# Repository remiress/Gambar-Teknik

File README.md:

# Hi I'm Raihan Emir
# I study at the State University of Yogyakarta

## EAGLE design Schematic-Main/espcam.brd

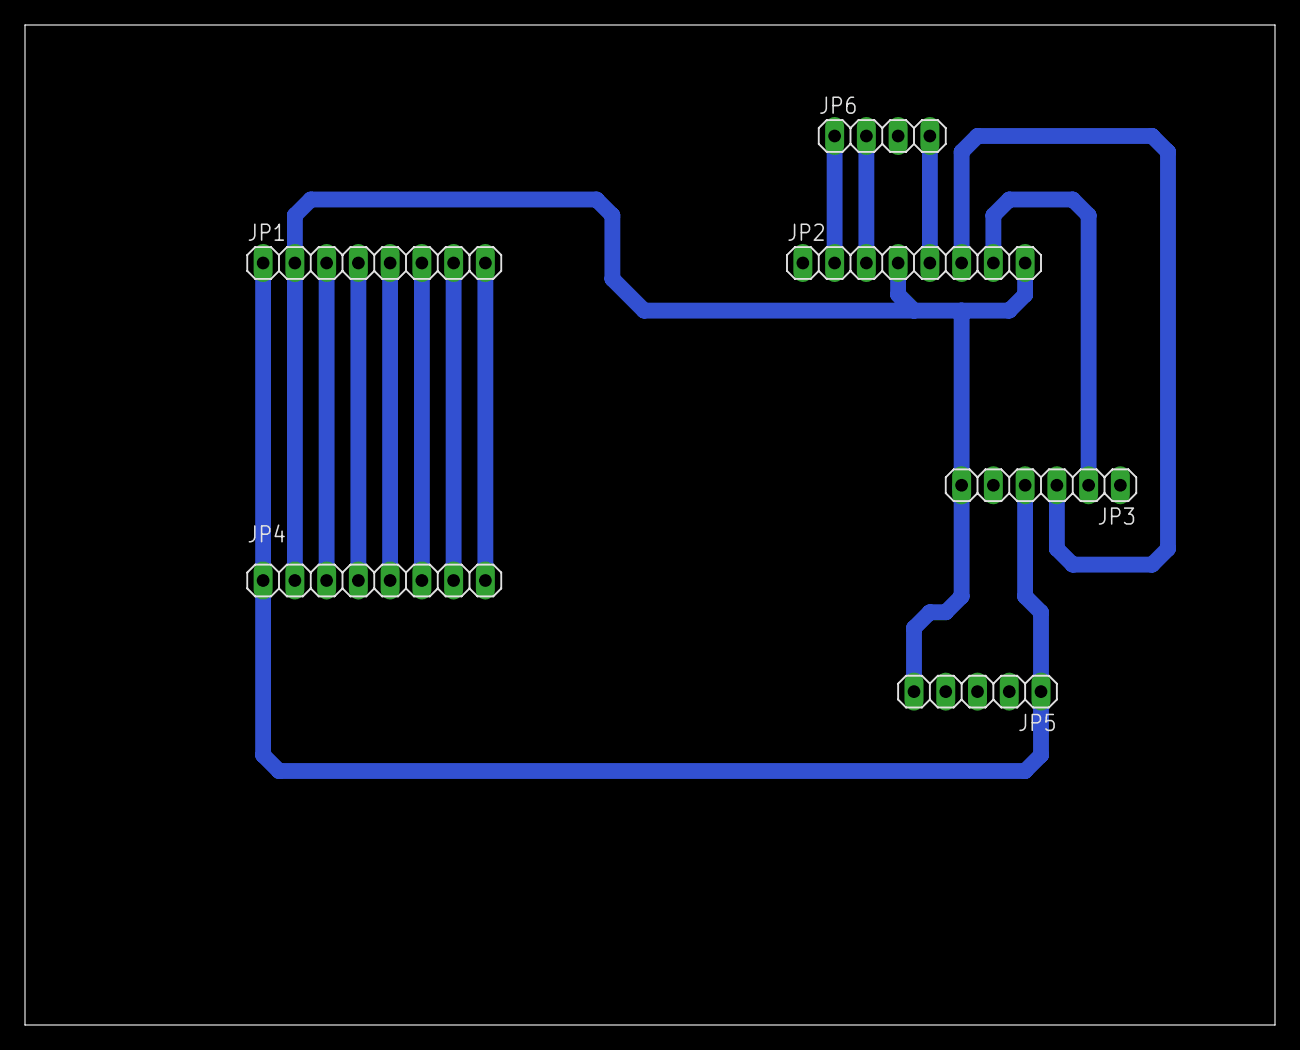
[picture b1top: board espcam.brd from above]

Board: 2 copper layers, 100.0 x 80.0 mm, 6 parts (0 on the bottom side), 13 nets.

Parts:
JP1, JP2, JP4: 1X08
JP3: 1X06
JP5: 1X05
JP6: 1X04

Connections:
5V: JP1.1, JP3.4, JP4.1, JP5.1
GND: JP1.2, JP2.4, JP2.8, JP3.6, JP4.2, JP5.5
IO0: JP2.3, JP6.2
IO2: JP1.7, JP4.7
IO4: JP1.8, JP4.8
IO12: JP1.3, JP4.3
IO13: JP1.4, JP4.4
IO14: JP1.6, JP4.6
IO15: JP1.5, JP4.5
IO16: JP2.2, JP6.1
RX: JP2.7, JP3.2
TX: JP2.6, JP3.3
VOUT: JP2.5, JP6.4

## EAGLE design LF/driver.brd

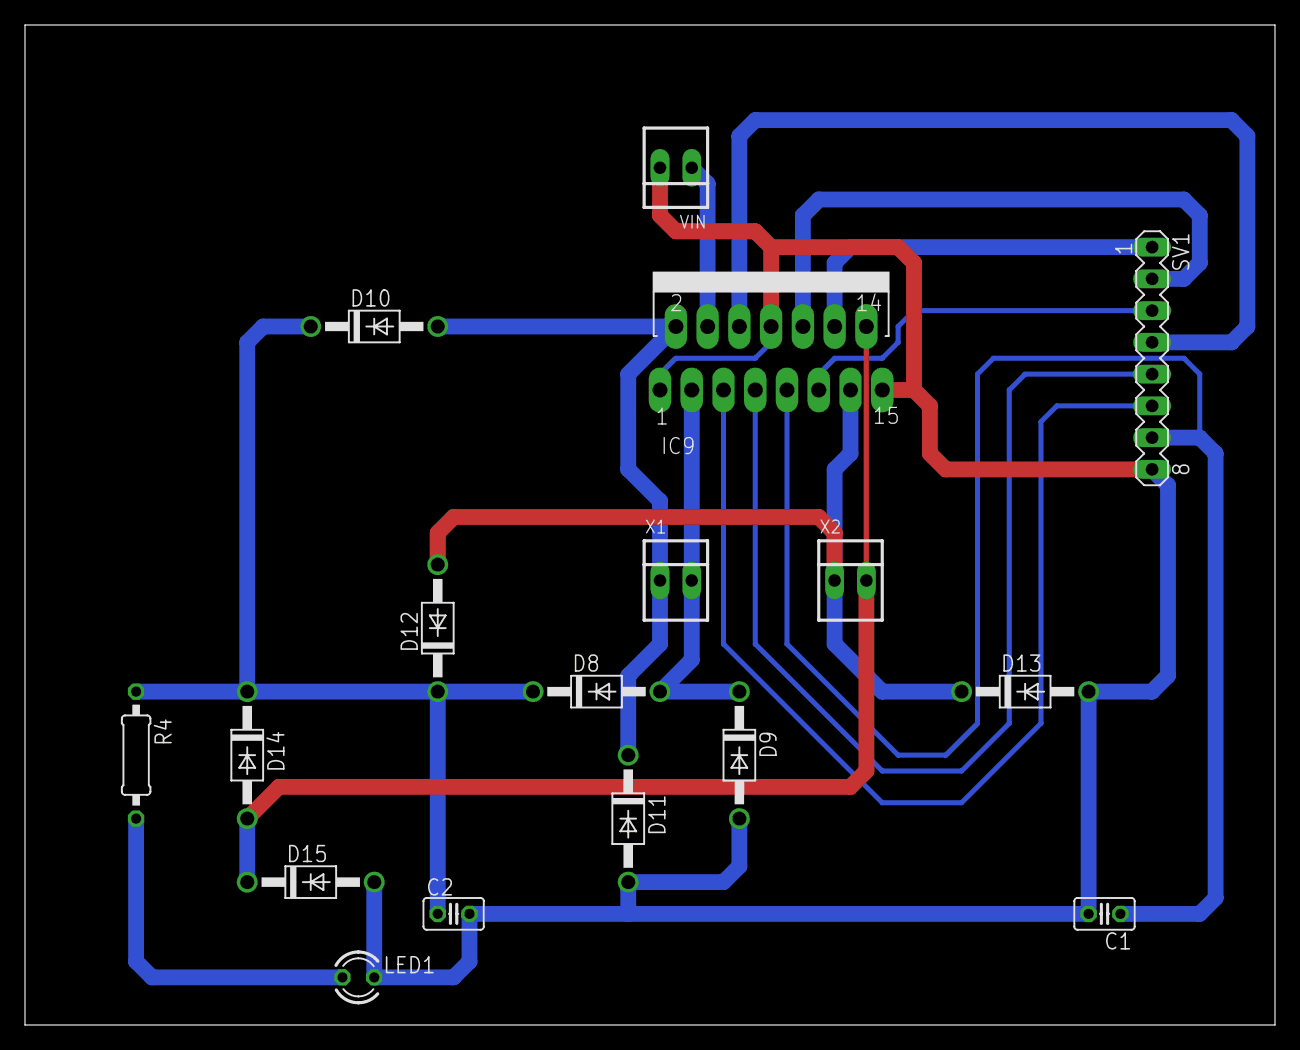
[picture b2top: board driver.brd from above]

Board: 2 copper layers, 100.0 x 80.0 mm, 17 parts (0 on the bottom side), 14 nets.

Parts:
C1, C2: 100nF; C025-025X050
D8, D9, D10, D11, D12, D13, D14, D15: 1N4004; DO41-10
IC9: L298; MULTIWATT-15
LED1: LED3MM
R4: 330; 0207/10
SV1: MA08-1
VIN: 22-23-2021
X1, X2: 22-23-2021

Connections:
GND: C1.2, C2.2, D9.A, D11.A, D13.A, D15.A, IC9.1, IC9.8, IC9.15, LED1.K, SV1.8, VIN.2
unnamed: IC9.5, SV1.6
unnamed: IC9.7, SV1.5
unnamed: IC9.12, SV1.1
unnamed: IC9.10, SV1.2
unnamed: IC9.6, SV1.4
unnamed: IC9.11, SV1.3
unnamed: LED1.A, R4.2
unnamed: D8.A, D9.C, IC9.3, X1.2
unnamed: D10.A, D11.C, IC9.2, X1.1
unnamed: D12.A, D13.C, IC9.13, X2.1
unnamed: D14.A, D15.C, IC9.14, X2.2
VCC: C1.1, IC9.9, SV1.7
VDD: C2.1, D8.C, D10.C, D12.C, D14.C, IC9.4, R4.1, VIN.1

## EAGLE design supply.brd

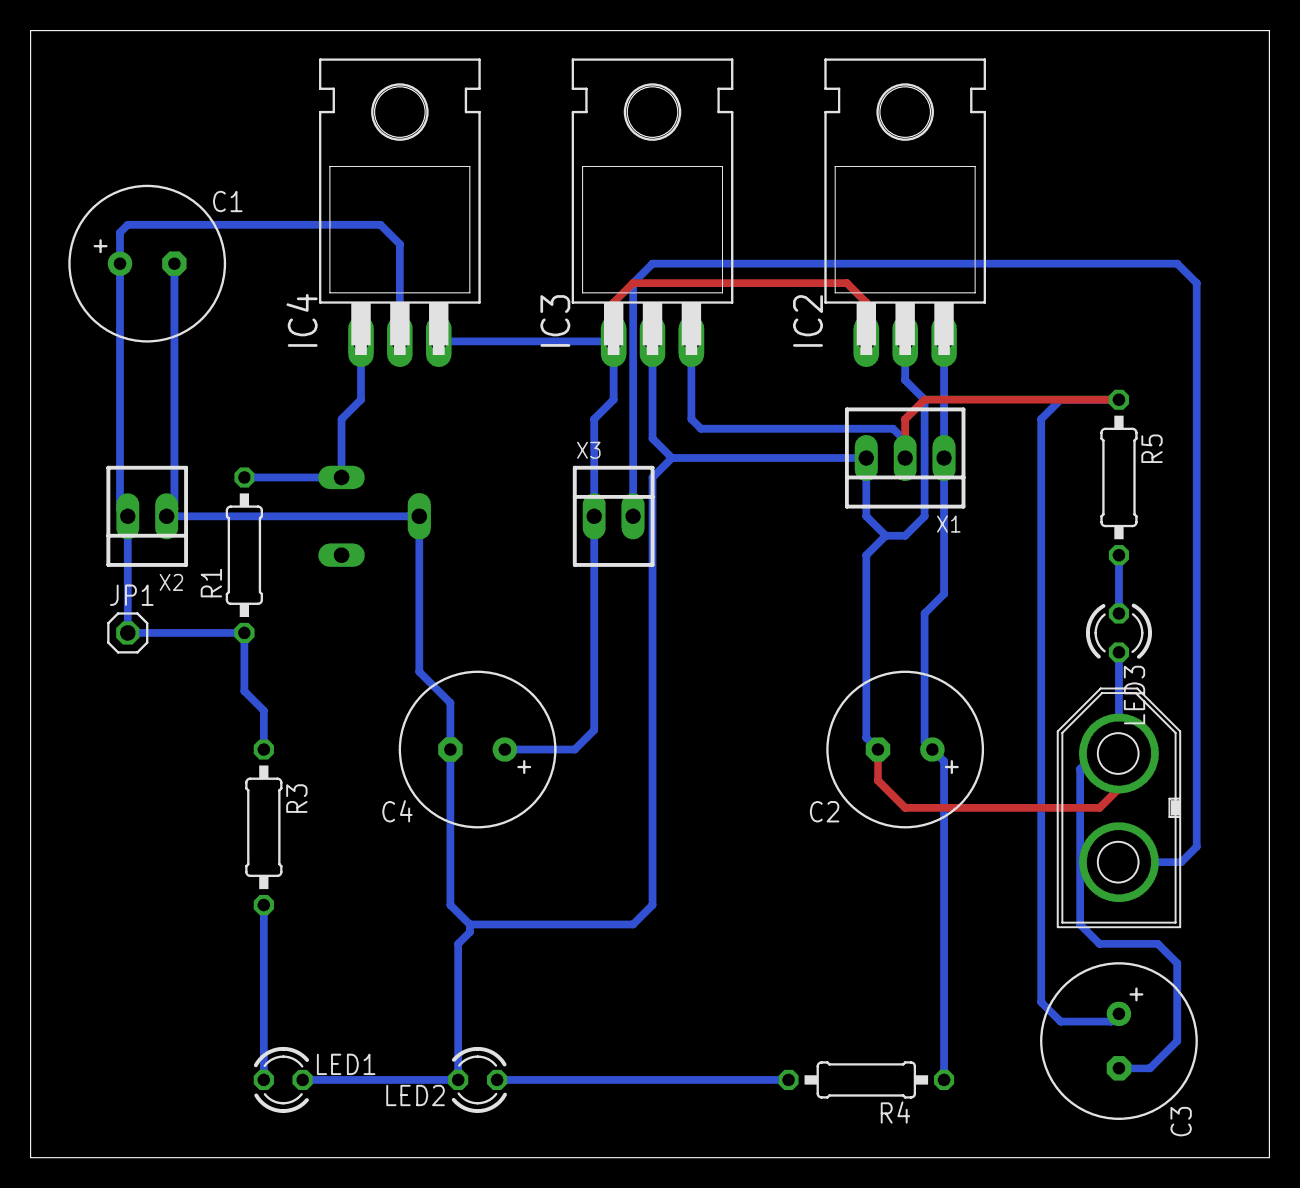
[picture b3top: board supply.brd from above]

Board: 2 copper layers, 81.0 x 73.7 mm, 20 parts (1 on the bottom side), 10 nets.

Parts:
C1, C2, C3, C4: 1000uF/16V; E3,5-10
IC2, IC3: 7805T; TO220H
IC4: 317T; TO220H
JP1: 1X01
LED1, LED2, LED3: LED3MM
R1: 1K2; 0207/10
R2: 20K; CA6V
R3, R4, R5: 1K; 0207/10
VIN: CON-XT60M
X1: VSYS; 22-23-2031
X2: VMOT; 22-23-2021
X3: switch; 22-23-2021

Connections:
+12V: C3.+, IC3.3, R5.1, X1.2
GND: C1.-, C2.-, C3.-, C4.-, IC2.2, IC3.2, LED1.K, LED2.K, LED3.K, R2.S, VIN.V-, X1.3, X2.1
unnamed: IC4.1, R1.2, R2.E
unnamed: LED1.A, R3.2
unnamed: LED3.A, R5.2
unnamed: VIN.V+, X3.2
unnamed: LED2.A, R4.2
VCC: C2.+, IC2.3, R4.1, X1.1
VDD: C1.+, IC4.2, JP1.1, R1.1, R3.1, X2.2
VPP: C4.+, IC2.1, IC3.1, IC4.3, X3.1

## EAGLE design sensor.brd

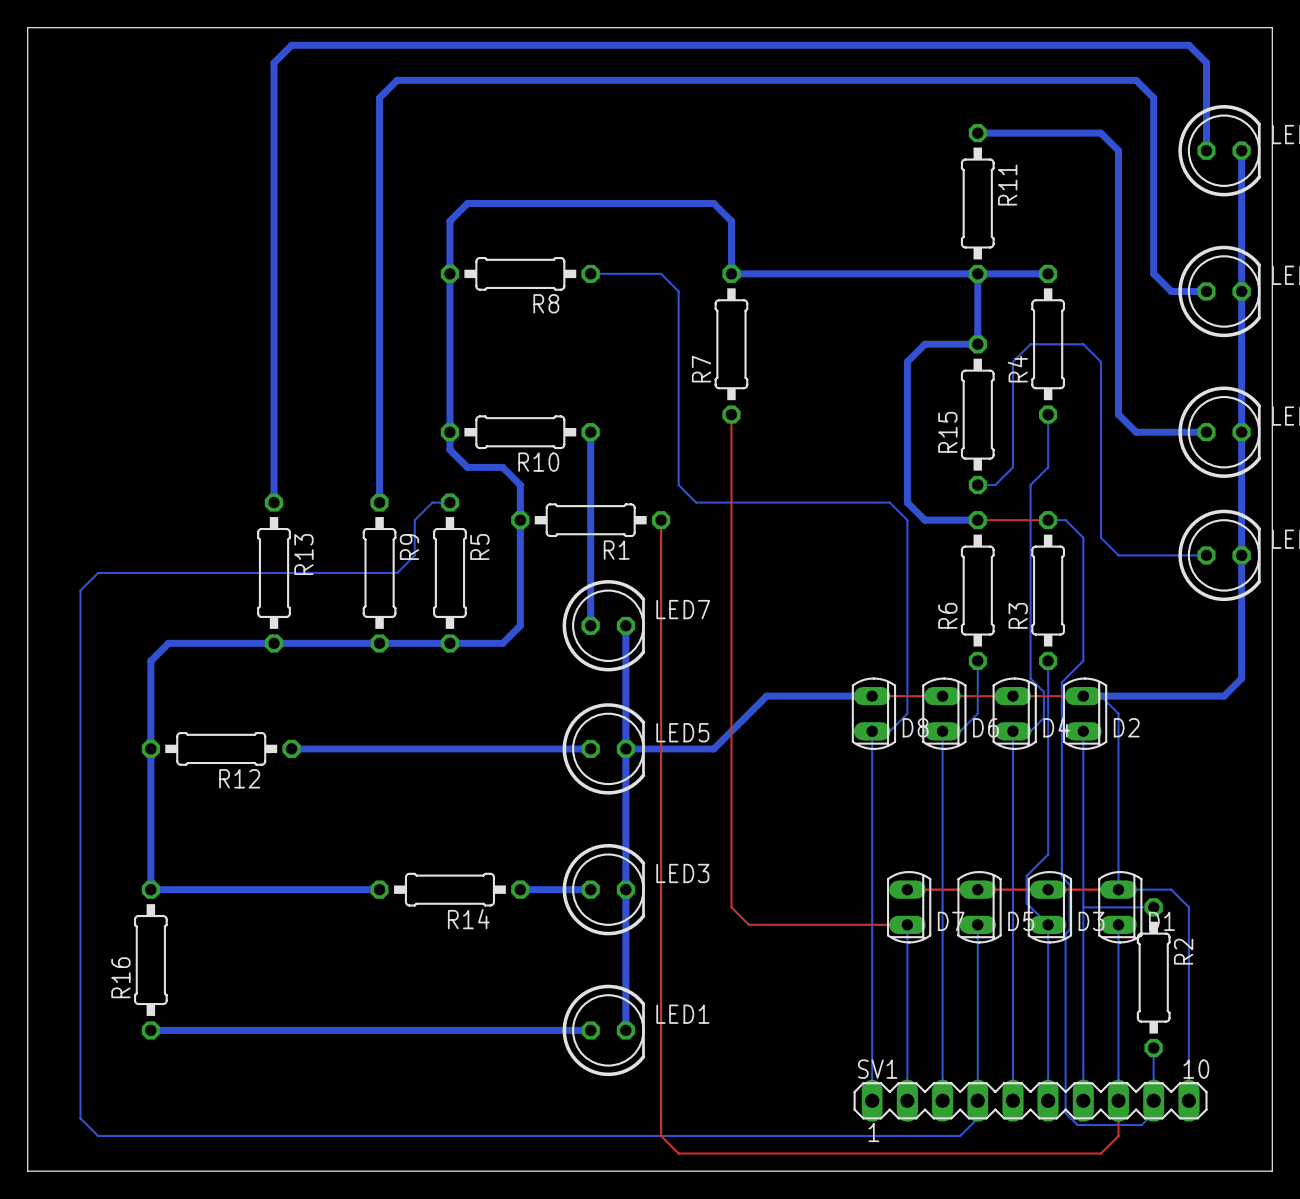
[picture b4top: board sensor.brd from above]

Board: 2 copper layers, 89.8 x 82.5 mm, 33 parts (0 on the bottom side), 18 nets.

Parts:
D1, D2, D3, D4, D5, D6, D7, D8: PhotoDioda; SFH225
LED1, LED2, LED3, LED4, LED5, LED6, LED7, LED8: LED putih SB; LED5MM
R1, R2, R3, R4, R5, R6, R7, R8: 0207/10
R9, R10, R11, R12, R13, R14, R15, R16: 330; 0207/10
SV1: MA10-1

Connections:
GND: D1.A, D2.A, D3.A, D4.A, D5.A, D6.A, D7.A, D8.A, LED1.K, LED2.K, LED3.K, LED4.K, LED5.K, LED6.K, LED7.K, LED8.K, SV1.10
unnamed: LED7.A, R10.1
unnamed: D7.K, R7.1, SV1.2
unnamed: D8.K, R8.1, SV1.1
unnamed: D1.K, R1.1, SV1.8
unnamed: D2.K, R2.1, SV1.7
unnamed: D3.K, R3.1, SV1.6
unnamed: D5.K, R5.1, SV1.4
unnamed: D4.K, R4.1, SV1.5
unnamed: D6.K, R6.1, SV1.3
unnamed: LED6.A, R11.1
unnamed: LED5.A, R12.1
unnamed: LED4.A, R13.1
unnamed: LED3.A, R14.1
unnamed: LED2.A, R15.1
unnamed: LED1.A, R16.1
unnamed: LED8.A, R9.1
VCC: R1.2, R2.2, R3.2, R4.2, R5.2, R6.2, R7.2, R8.2, R9.2, R10.2, R11.2, R12.2, R13.2, R14.2, R15.2, R16.2, SV1.9

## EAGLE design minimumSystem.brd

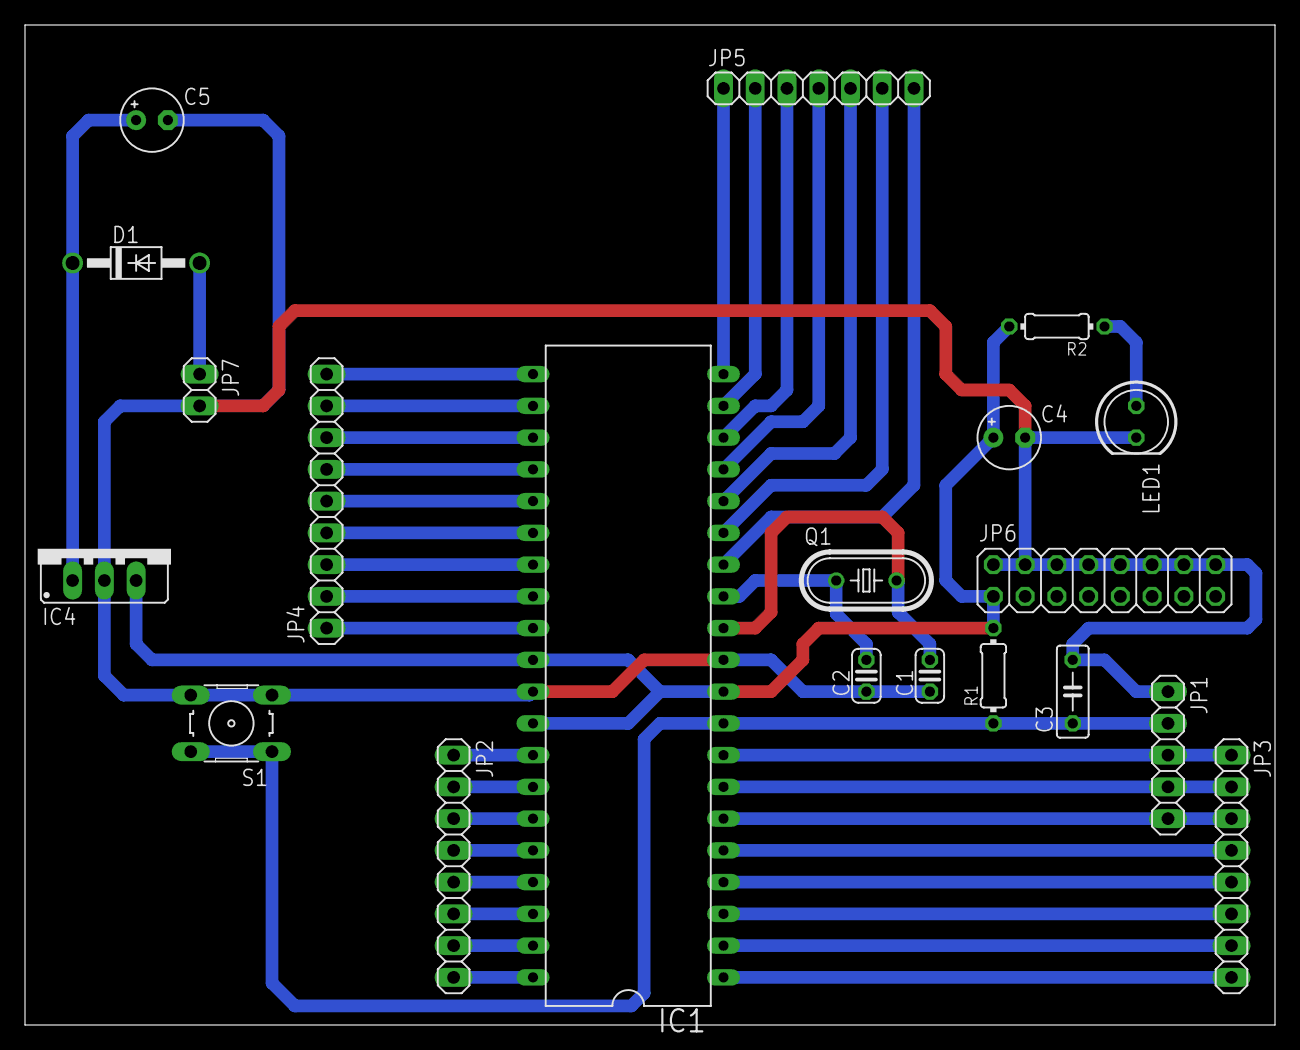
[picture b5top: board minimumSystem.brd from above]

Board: 2 copper layers, 100.0 x 80.0 mm, 20 parts (0 on the bottom side), 40 nets.

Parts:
C1, C2: C025-024X044
C3: C050-025X075
C4, C5: E2,5-5
D1: 1N4004; DO41-10
IC1: MEGA16-P; DIL40
IC4: 78XXS
JP1: 1X05
JP2, JP3: 1X08
JP4: 1X09
JP5: 1X07
JP6: 2X08
JP7: 1X02
LED1: LED5MM
Q1: HC49U-V
R1, R2: 0204/7
S1: B3F-10XX

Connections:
+5V: C4.+, IC1.10, IC1.30, IC1.32, IC4.OUT, JP6.1, JP6.3, JP6.5, JP6.7, JP6.9, JP6.11, JP6.13, JP6.15, R1.2, R2.2
+12V: D1.A, JP7.1
C0: IC1.22, JP4.8
C1: IC1.23, JP4.7
C2: IC1.24, JP4.6
C3: IC1.25, JP4.5
D7: IC1.14, JP5.7
GND: C1.1, C2.1, C3.2, C4.-, C5.-, IC1.11, IC1.31, IC4.GND, JP1.1, JP6.2, JP6.4, JP6.6, JP6.8, JP6.10, JP6.12, JP6.14, JP6.16, JP7.2, LED1.K, S1.3, S1.4
unnamed: IC1.33, JP2.1
unnamed: IC1.34, JP2.2
unnamed: IC1.35, JP2.3
unnamed: IC1.36, JP2.4
unnamed: IC1.37, JP2.5
unnamed: IC1.38, JP2.6
unnamed: IC1.39, JP2.7
unnamed: IC1.40, JP2.8
unnamed: IC1.29, JP4.1
unnamed: IC1.28, JP4.2
unnamed: IC1.27, JP4.3
unnamed: IC1.5, JP3.4
unnamed: IC1.20, JP5.1
unnamed: IC1.19, JP5.2
unnamed: IC1.26, JP4.4
unnamed: IC1.6, JP1.5, JP3.3
unnamed: IC1.4, JP3.5
unnamed: IC1.3, JP3.6
unnamed: IC1.2, JP3.7
unnamed: IC1.1, JP3.8
unnamed: C5.+, D1.C, IC4.IN
unnamed: IC1.15, JP5.6
unnamed: IC1.16, JP5.5
unnamed: IC1.17, JP5.4
unnamed: C3.1, IC1.9, JP1.2, R1.1, S1.1, S1.2
unnamed: IC1.18, JP5.3
unnamed: C1.2, IC1.12, Q1.2
unnamed: C2.2, IC1.13, Q1.1
unnamed: LED1.A, R2.1
unnamed: IC1.8, JP1.3, JP3.1
unnamed: IC1.7, JP1.4, JP3.2
RS: IC1.21, JP4.9

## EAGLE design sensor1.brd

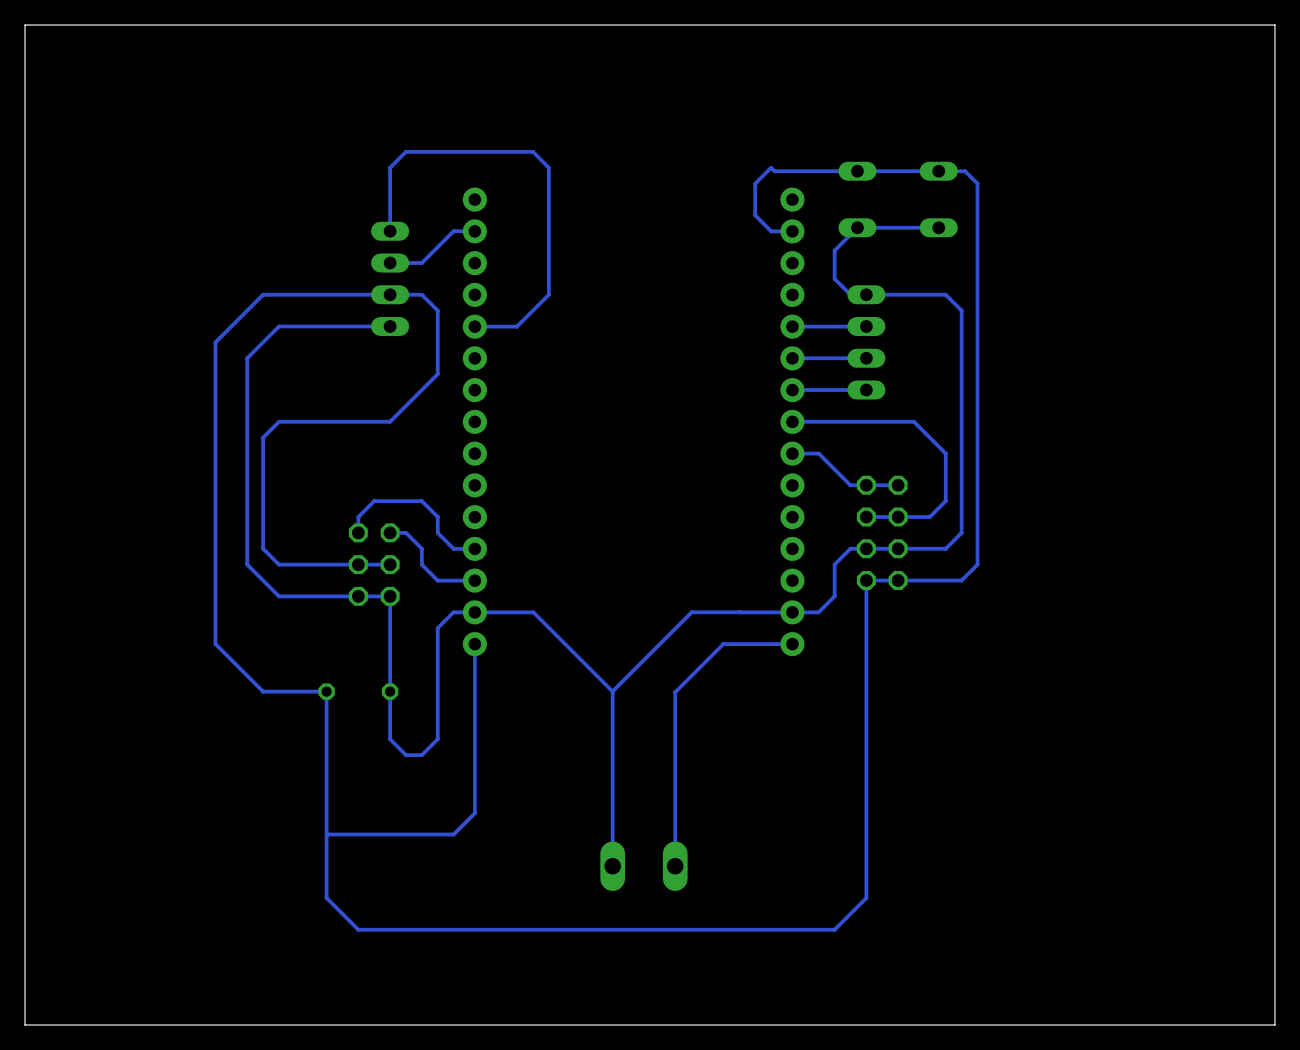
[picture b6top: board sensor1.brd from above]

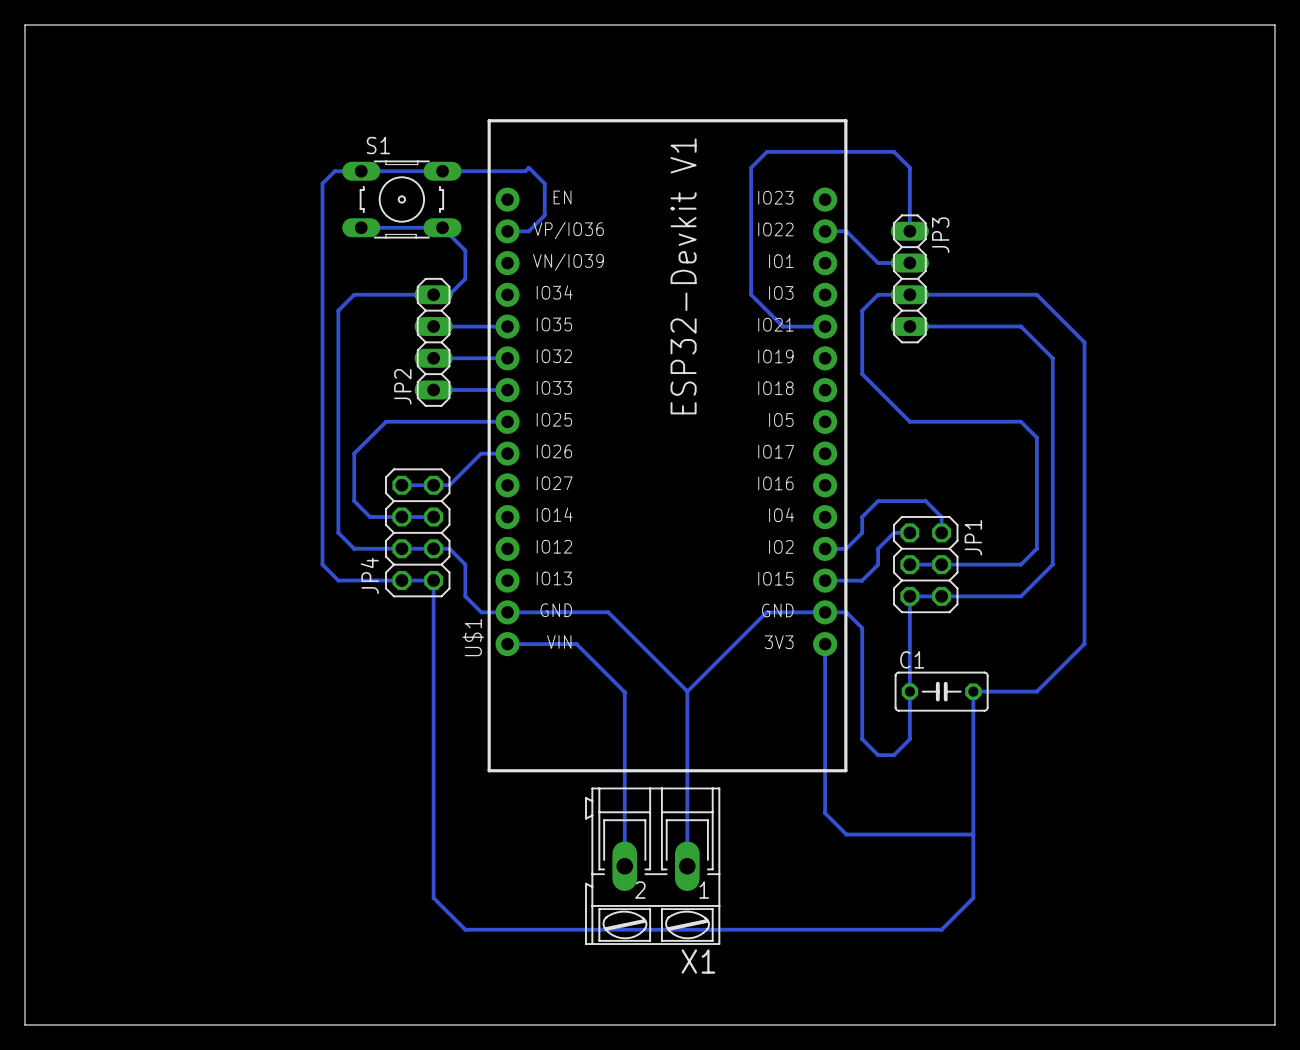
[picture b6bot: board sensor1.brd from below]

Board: 2 copper layers, 100.0 x 80.0 mm, 8 parts (8 on the bottom side), 12 nets.

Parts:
C1: C050-030X075
JP1: 2X03
JP2, JP3: 1X04
JP4: 2X04
S1: B3F-10XX
U$1: ESP32DEVKITV1; ESP32-DEVKITV1
X1: AK300/2

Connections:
GND: C1.1, JP1.5, JP1.6, JP2.4, JP3.4, JP4.3, JP4.4, S1.3, S1.4, U$1.GND@1, U$1.GND@2, X1.1
MOISTURE: JP1.2, U$1.D2
OUT1: JP2.1, U$1.D33
OUT2: JP2.2, U$1.D32
OUT3: JP2.3, U$1.D35
PH: JP1.1, U$1.D15
SCL: JP3.2, U$1.D22
SCL2: JP4.5, JP4.6, U$1.D25
SDA: JP3.1, U$1.D21
SDA2: JP4.7, JP4.8, U$1.D26
V: C1.2, JP1.3, JP1.4, JP3.3, JP4.1, JP4.2, S1.1, S1.2, U$1.3V3, U$1.D36
VIN: U$1.VIN, X1.2

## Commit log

2021-11-24 Create Tugas Rangkaian
2021-11-24 Create Tugas FL
2021-12-23 Rename driver.brd to LF/driver.brd
2021-12-23 Rename sensor.brd to LF/sensor.brd
2021-12-23 Rename supply.brd to LF/supply.brd
2021-12-23 Rename espcam.brd to Schematic-Main/espcam.brd
2021-12-23 Rename sensor.sch to Schematic-Main/sensor.sch
2021-12-23 Rename sensor1.brd to Schematic-Main/sensor1.brd
2021-12-23 Rename tugas 1 schematic.sch to Schematic-Main/tugas 1 schematic.sch
2021-12-23 Rename Tugas arduino sensor.sch to Arduino/Tugas arduino sensor.sch
